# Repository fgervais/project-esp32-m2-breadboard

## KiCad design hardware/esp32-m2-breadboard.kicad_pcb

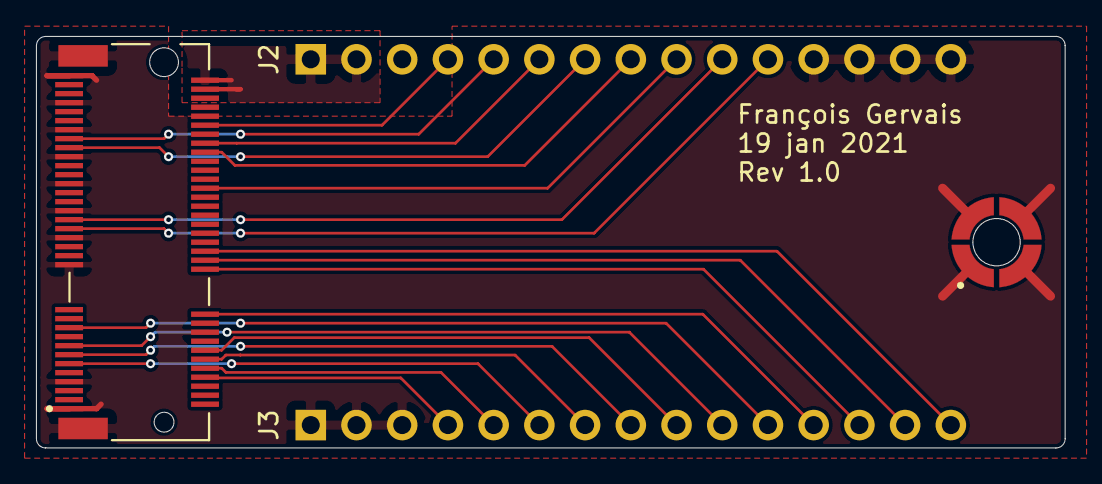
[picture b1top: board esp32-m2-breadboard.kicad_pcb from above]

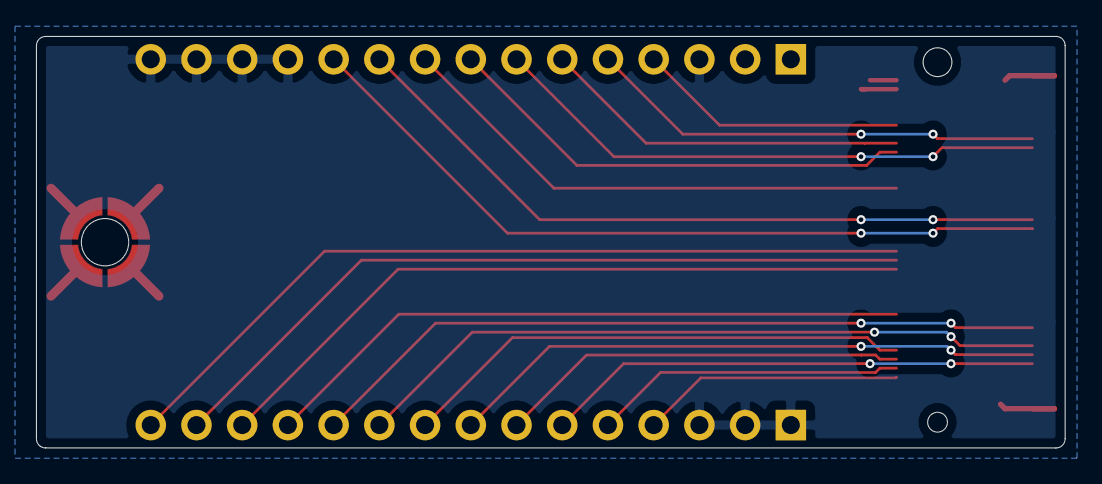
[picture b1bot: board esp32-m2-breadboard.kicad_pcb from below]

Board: 2 copper layers, 57.2 x 22.9 mm, 4 parts (2 on the bottom side), 22 nets.

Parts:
J1: 2199230-4; TE_2199230-4
J2, J3: Conn_01x15_Female; PinHeader_1x15_P2.54mm_Vertical
MP1: SM3ZS067U410-NUT1-R1200; JAE_SM3ZS067U410-NUT1-R1200

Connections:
+5V: J1.72, J1.74, J2.1, J2.2
/DTR: J1.36, J3.15
/GPIO2: J1.13, J3.8
/GPIO4: J1.15, J3.10
/GPIO5: J1.14, J3.9
/GPIO15: J1.11, J3.6
/GPIO16: J1.19, J3.11
/GPIO18: J1.8, J3.4
/GPIO19: J1.10, J3.5
/GPIO21: J1.43, J2.10
/GPIO22: J1.41, J2.11
/GPIO23: J1.12, J3.7
/GPIO25-DAC1: J1.64, J2.4
/GPIO26-DAC2: J1.61, J2.5
/GPIO27: J1.59, J2.7
/GPIO32: J1.58, J2.8
/GPIO33: J1.60, J2.6
/RESET: J1.50, J2.9
/RTS: J1.34, J3.14
/RX: J1.32, J3.13
/TX: J1.22, J3.12
GND: J1.1, J1.7, J1.18, J1.33, J1.39, J1.45, J1.51, J1.57, J1.63, J1.69, J1.75, J1.S1, J1.S2, J2.3, J2.12, J2.13, J2.14, J2.15, J3.1, J3.2, J3.3, MP1.1, MP1.2, MP1.3, MP1.4

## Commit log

2021-01-18 Add kicad-library submodule
2021-01-18 Parts in schematic and first placement
2021-01-18 Pins assigned
2021-01-19 First routing done
2021-01-19 Add name,date,rev on silkscreen
2021-01-19 Show bottom layer
2021-01-20 Set version of previous commit to board
